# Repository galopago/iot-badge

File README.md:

# IOT-BADGE

## Electronic conference badge for programming conventions, hacking events, etc.

* Open Source (designed in [KiCad](https://www.kicad.org/)), schematic files, PCB and GERBER files open, free and available
* Comfortable wearable badge, no components on the back side.
* Max size 10 x 10 cm to take advantage of cost reductions of most PCB makers.
* Can be powered by a 3.2 v LiFePO4 AAA size battery
* Compatible with TinyGS firmware for [reception of LoRa satellites](https://galopago.github.io/english/lora-satelite-ground-station/). No modifications needed!

Read this in other languages: [Español](/iot-badge-433/assets/markdown/README.es.md)

## Block Diagram

## Capabilities

* ESP32 module compatible with multiple programming languages/platforms: [C/C++](https://docs.espressif.com/projects/esp-idf/en/latest/esp32/), [Arduino](https://github.com/espressif/arduino-esp32), Python (via [MicroPython](https://micropython.org/)), JavaScript (via [Espruino](https://www.espruino.com/ESP32) or [Mongoose OS](https://mongoose-os.com/)), [Rust ([via esp-rs](https://esp-rs.github.io/book/))
* 0.96" OLED display
* Infrared LED transmitter and receiver
* WiFi
* Radio transmitter and receiver module: FSK, GFSK, MSK, GMSK and LoRa!
* Onboard PCB antenna (433 Mhz and 915 Mhz versions)
* U.FL Connector for external antenna
* RGB LED
* 0.7 W speaker
* 6 buttons: 4 arranged in D-pad and 2 function buttons
* USB-C Connector

## 433 Mhz Version
Back                           | Side                                  | External Ant                          |
-------------------------------|---------------------------------------|---------------------------------------|
| | |

## Schematic Diagram 433 Version

## Pinout connections

### SSD1306 128x64 i2c OLED display

ESP32 GPIO PIN |Function
---------------|---------
4              | SDA
15             | SCL

### Ra-02 LoRa module

ESP32 GPIO PIN |Function
---------------|---------
19             | POCI
27             | PICO
5              | SCK
18             | /CS

### Speaker

ESP32 GPIO PIN |Function
---------------|---------
25             | Speaker

### Buttons ( please use internal pull-ups! )

ESP32 GPIO PIN |Function
---------------|---------
0              | Up
13             | Down
16             | Left
17             | Right
33             | B
32             | A

### RGB LED

ESP32 GPIO PIN |Function
---------------|---------
21             | Red
22             | Green
23             | Blue

### Ifrared transmitter LED

ESP32 GPIO PIN |Function
---------------|---------
2              | Infrared LED

### VS1838b INFRARED RECEIVER MODULE

ESP32 GPIO PIN |Function
---------------|---------
12             | VS1838b output

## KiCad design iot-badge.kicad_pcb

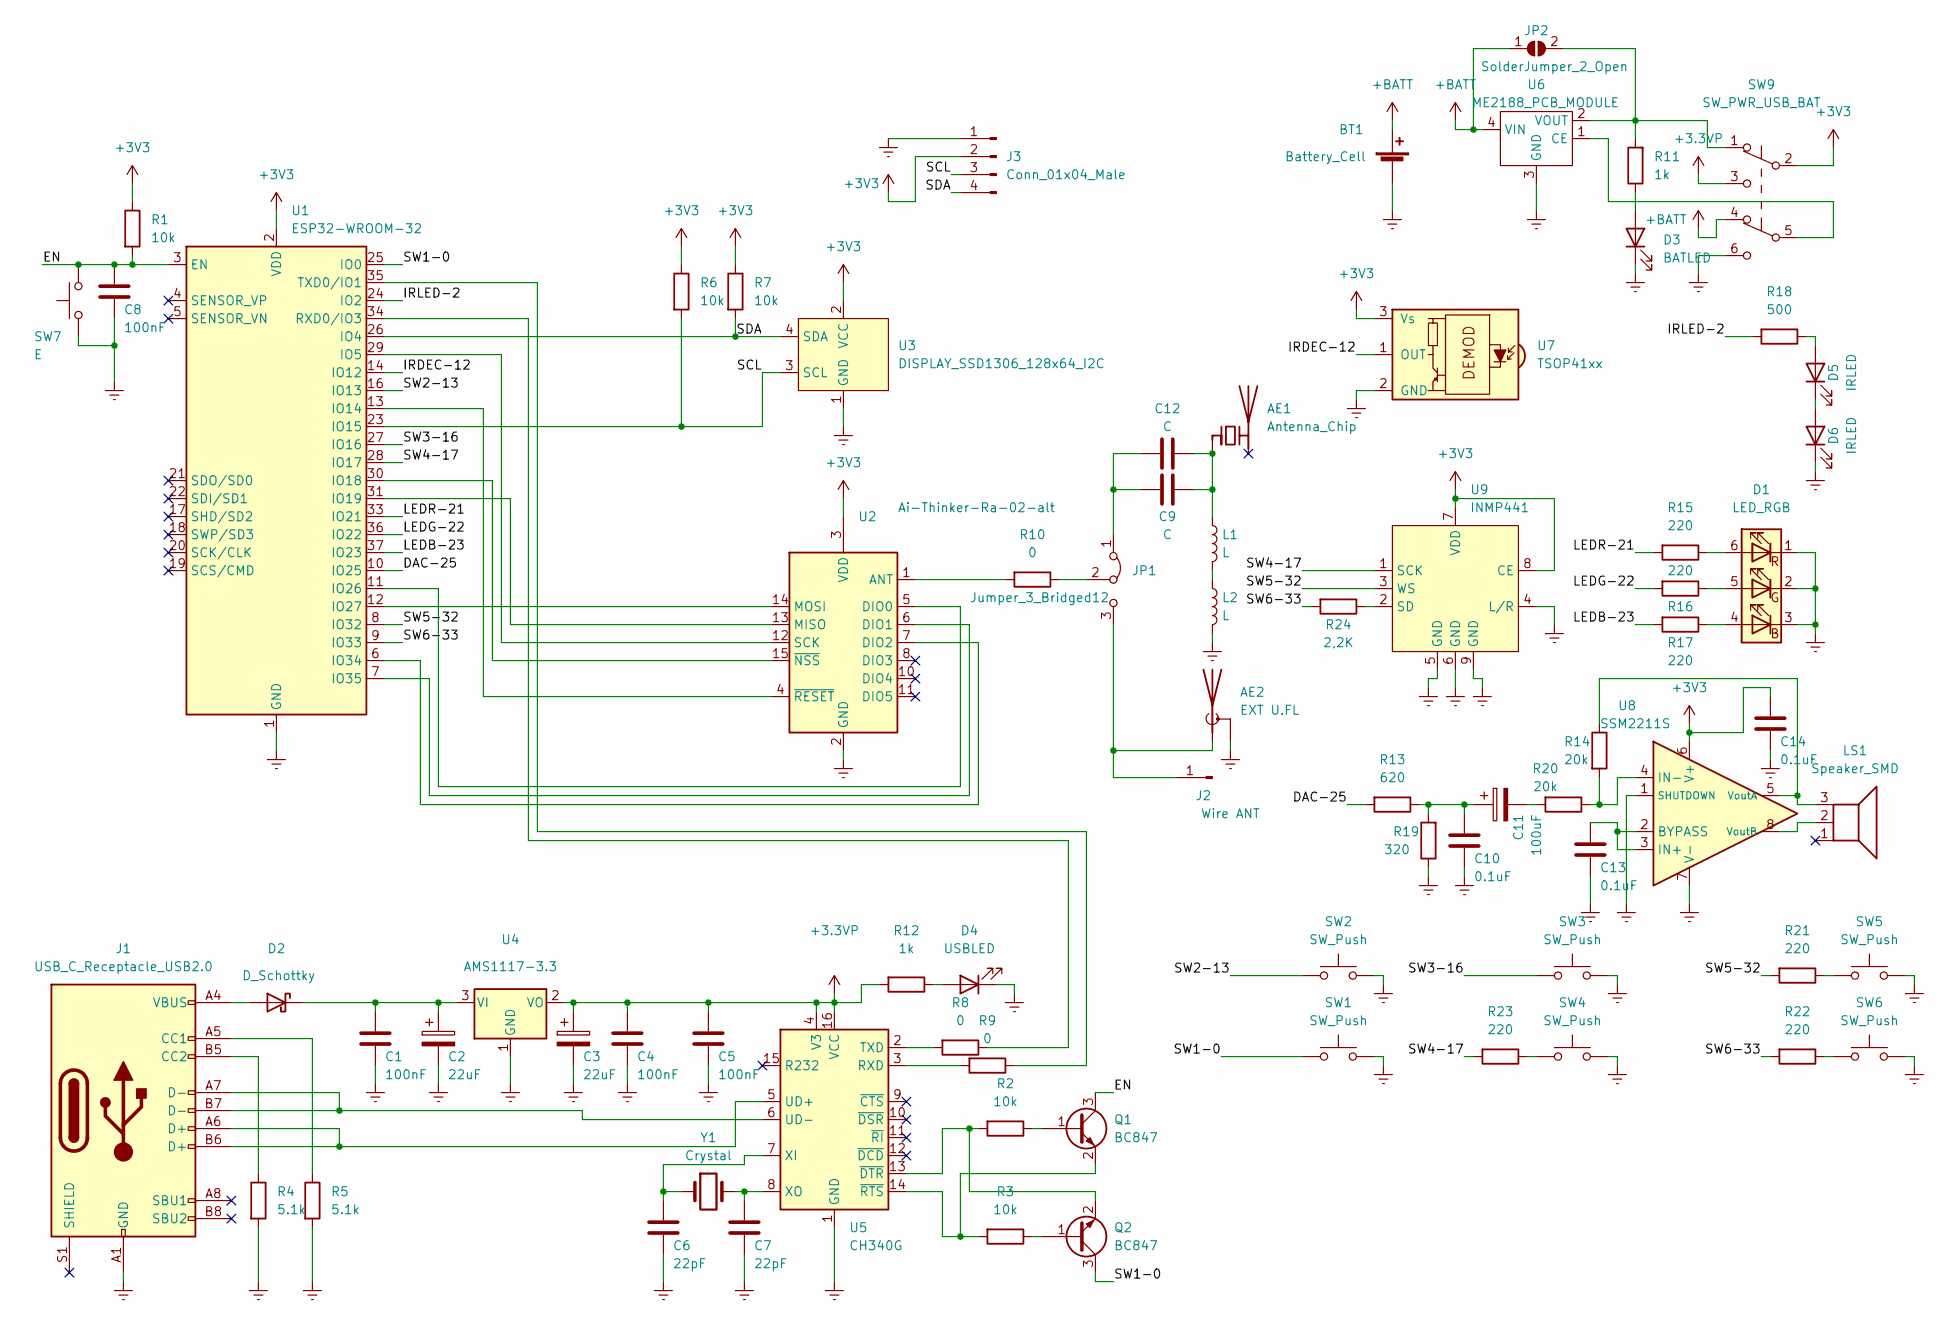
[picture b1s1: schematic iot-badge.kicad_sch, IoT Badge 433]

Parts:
AE1: Antenna_Chip; Crossair_ca-s01
AE2: EXT U.FL; U.FL_Hirose_U.FL-R-SMT-1_Vertical
BT1: Battery_Cell; BatteryHolder_Keystone_1022_2xAAA
C1, C4, C5, C8: 100nF; C_0805_2012Metric_Pad1.18x1.45mm_HandSolder
C2, C3: 22uF; CP_EIA-2012-15_AVX-P_Pad1.30x1.05mm_HandSolder
C6, C7: 22pF; C_0805_2012Metric_Pad1.18x1.45mm_HandSolder
C9, C12: C; C_0805_2012Metric_Pad1.18x1.45mm_HandSolder
C10, C13, C14: 0.1uF; C_0805_2012Metric_Pad1.18x1.45mm_HandSolder
C11: 100uF; CP_EIA-2012-15_AVX-P_Pad1.30x1.05mm_HandSolder
D1: LED_RGB; LED_RGB_5050-6
D2: D_Schottky; D_SOD-123
D3: BATLED; LED_0805_2012Metric_Pad1.15x1.40mm_HandSolder
D4: USBLED; LED_0805_2012Metric_Pad1.15x1.40mm_HandSolder
D5, D6: IRLED; LED_0805_2012Metric_Pad1.15x1.40mm_HandSolder
J1: USB_C_Receptacle_USB2.0; USB_C_Receptacle_HRO_TYPE-C-31-M-12
J2: Wire ANT; PinHeader_1x01_P1.00mm_Vertical
J3: Conn_01x04_Male; PinHeader_1x04_P2.54mm_Vertical
JP1: Jumper_3_Bridged12; SolderJumper-3_P1.3mm_Bridged12_RoundedPad1.0x1.5mm_NumberL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
JP2: SolderJumper_2_Open; SolderJumper-2_P1.3mm_Open_RoundedPad1.0x1.5mm
L1, L2: L; L_0805_2012Metric_Pad1.05x1.20mm_HandSolder
LS1: Speaker_SMD; Speaker_SMD-5020
Q1, Q2: BC847; SOT-23
R1, R2, R3, R6, R7: 10k; R_0805_2012Metric_Pad1.20x1.40mm_HandSolder
R4, R5: 5.1k; R_0805_2012Metric_Pad1.20x1.40mm_HandSolder
R8, R9, R10: 0; R_0805_2012Metric_Pad1.20x1.40mm_HandSolder
R11, R12: 1k; R_0805_2012Metric_Pad1.20x1.40mm_HandSolder
R13: 620; R_0805_2012Metric_Pad1.20x1.40mm_HandSolder
R14, R20: 20k; R_0805_2012Metric_Pad1.20x1.40mm_HandSolder
R15, R16, R17, R21, R22, R23: 220; R_0805_2012Metric_Pad1.20x1.40mm_HandSolder
R18: 500; R_0805_2012Metric_Pad1.20x1.40mm_HandSolder
R19: 320; R_0805_2012Metric_Pad1.20x1.40mm_HandSolder
R24: 2,2K; R_0805_2012Metric_Pad1.20x1.40mm_HandSolder
SW1, SW2, SW3, SW4, SW5, SW6: SW_Push; SW_Push_1P1T_NO_6x6mm_H9.5mm
SW7: E; SW_Push_SPST_NO_Alps_SKRK
SW9: SW_PWR_USB_BAT; SW_Slide_2P2T_9mmx7.6mm
U1: ESP32-WROOM-32
U2: Ai-Thinker-Ra-02-alt; Ai-Thinker-Ra-02-LoRa-alt
U3: DISPLAY_SSD1306_128x64_I2C; DISPLAY_SSD1306_128x64_I2C_0.96inch
U4: AMS1117-3.3; SOT-223-3_TabPin2
U5: CH340G; SOIC-16_3.9x9.9mm_P1.27mm
U6: ME2188_PCB_MODULE
U7: TSOP41xx; Vishay_MOLD-3Pin
U8: SSM2211S; SOIC-8_3.9x4.9mm_P1.27mm
U9: INMP441
Y1: Crystal; Crystal_SMD_HC49-SD_HandSoldering_Compact

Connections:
+3.3VP: C3.1, C4.1, C5.1, R12.2, SW9.3 (C), U4.2 (VO), U5.4 (V3), U5.16 (VCC)
+3V3: C14.1, J3.2, R1.1, R6.1, R7.1, SW9.2 (B), U1.2 (VDD), U2.3 (VDD), U3.2 (VCC), U7.3 (Vs), U8.6 (V+), U9.7 (VDD), U9.8 (CE)
+BATT: BT1.1 (+), JP2.1 (A), SW9.4 (A), U6.4 (VIN)
/DAC-25: R13.2, U1.10 (IO25)
/EN: C8.1, Q1.3 (C), R1.2, SW7.2, U1.3 (EN)
/IRDEC-12: U1.14 (IO12), U7.1 (OUT)
/IRLED-2: R18.2, U1.24 (IO2)
/LEDB-23: R17.2, U1.37 (IO23)
/LEDG-22: R16.2, U1.36 (IO22)
/LEDR-21: R15.2, U1.33 (IO21)
/SCL: J3.3, R6.2, U1.23 (IO15), U3.3 (SCL)
/SDA: J3.4, R7.2, U1.26 (IO4), U3.4 (SDA)
/SW1-0: Q2.3 (C), SW1.1, U1.25 (IO0)
/SW2-13: SW2.1, U1.16 (IO13)
/SW3-16: SW3.1, U1.27 (IO16)
/SW4-17: R23.2, U1.28 (IO17), U9.1 (SCK)
/SW5-32: R21.2, U1.8 (IO32), U9.3 (WS)
/SW6-33: R22.2, R24.2, U1.9 (IO33)
Earth: AE2.2 (Shield), BT1.2 (-), C1.2, C2.2, C3.2, C4.2, C5.2, C6.2, C7.2, C8.2, C10.2, C13.2, C14.2, D1.1 (RK), D1.2 (GK), D1.3 (BK), D3.1 (K), D4.1 (K), D6.1 (K), J1.A1 (GND), J1.A12 (GND), J1.B1 (GND), J1.B12 (GND), J3.1, L2.2, R4.2, R5.2, R19.1, SW1.2, SW2.2, SW3.2, SW4.2, SW5.2, SW6.2, SW7.1, SW9.6 (C), U1.1 (GND), U1.15 (GND), U1.38 (GND), U1.39 (GND), U2.2 (GND), U2.9 (GND), U2.16 (GND), U3.1 (GND), U4.1 (GND), U5.1 (GND), U6.3 (GND), U7.2 (GND), U8.1 (SHUTDOWN), U8.7 (V-), U9.4 (L/R), U9.5 (GND), U9.6 (GND), U9.9 (GND)
unnamed: AE1.1 (FEED), C9.1, C12.1, L1.1
unnamed: AE2.1 (A), J2.1, JP1.3 (B)
unnamed: C1.1, C2.1, D2.1 (K), U4.3 (VI)
unnamed: C6.1, U5.7 (XI), Y1.1
unnamed: C7.1, U5.8 (XO), Y1.2
unnamed: C10.1, C11.1, R13.1, R19.2
unnamed: C11.2, R20.2
unnamed: C9.2, C12.2, JP1.1 (A)
unnamed: C13.1, U8.2 (BYPASS), U8.3 (IN+)
unnamed: D1.4 (BA), R17.1
unnamed: D1.5 (GA), R16.1
unnamed: D1.6 (RA), R15.1
unnamed: D2.2 (A), J1.A4 (VBUS), J1.A9 (VBUS), J1.B4 (VBUS), J1.B9 (VBUS)
unnamed: D3.2 (A), R11.1
unnamed: D4.2 (A), R12.1
unnamed: D5.1 (K), D6.2 (A)
unnamed: D5.2 (A), R18.1
unnamed: J1.A5 (CC1), R5.1
unnamed: J1.A6 (D+), J1.B6 (D+), U5.5 (UD+)
unnamed: J1.A7 (D-), J1.B7 (D-), U5.6 (UD-)
unnamed: J1.B5 (CC2), R4.1
unnamed: JP1.2 (C), R10.1
unnamed: JP2.2 (B), R11.2, SW9.1 (A), U6.2 (VOUT)
unnamed: L1.2, L2.1
unnamed: LS1.2, U8.8 (VoutB)
unnamed: LS1.3, R14.1, U8.5 (VoutA)
unnamed: Q1.1 (B), R2.1
unnamed: Q1.2 (E), R3.2, U5.14 (~RTS)
unnamed: Q2.1 (B), R3.1
unnamed: Q2.2 (E), R2.2, U5.13 (~DTR)
unnamed: R8.1, U1.34 (RXD0/IO3)
unnamed: R8.2, U5.2 (TXD)
unnamed: R9.1, U1.35 (TXD0/IO1)
unnamed: R9.2, U5.3 (RXD)
unnamed: R10.2, U2.1 (ANT)
unnamed: R14.2, R20.1, U8.4 (IN-)
unnamed: R21.1, SW5.1
unnamed: R22.1, SW6.1
unnamed: R23.1, SW4.1
unnamed: R24.1, U9.2 (SD)
unnamed: SW9.5 (B), U6.1 (CE)
unnamed: U1.6 (IO34), U2.7 (DIO2)
unnamed: U1.7 (IO35), U2.6 (DIO1)
unnamed: U1.11 (IO26), U2.5 (DIO0)
unnamed: U1.12 (IO27), U2.14 (MOSI)
unnamed: U1.13 (IO14), U2.4 (~RESET)
unnamed: U1.29 (IO5), U2.12 (SCK)
unnamed: U1.30 (IO18), U2.15 (~NSS)
unnamed: U1.31 (IO19), U2.13 (MISO)

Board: 2 copper layers, 77 parts (1 on the bottom side), 68 nets, no tracks yet.

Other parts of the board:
SYMB1: OSHW-Symbol_6.7x6mm_Copper
SYMB2: OSHW-Symbol_6.7x6mm_SilkScreen

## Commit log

2023-01-29 added first proof of concept
2023-01-29 added first blockdiag
2023-02-26 added mic to blockdiag
2023-02-27 started readme
2023-02-27 started readme+
2023-03-01 started micrel pcb helix ant 433
2023-03-07 pcb antenna finished
2023-03-09 i2c display footprint started
2023-03-14 improved holding holes
2023-03-14 changed battery for AAA
2023-03-15 added some USB components
2023-03-22 ant needs some care NETS
2023-03-25 ant needs routing rules
2023-03-26 pcb ant fixed
2023-03-29 connected lora and screen
2023-03-31 added res buttons and almost routable
2023-04-19 added crystal and led rgb
2023-04-21 diode added to power
2023-04-26 added external ant
2023-04-29 power switch added
2023-05-01 added ground to pushbuttons
2023-05-02 started batt footprint
2023-05-03 all elements placed and wired
2023-05-04 silk improvements
2023-05-05 all wired, unable to route
2023-05-06 all wired, routed
2023-05-06 all wired, routed,fixes
2023-05-08 finished pcb
2023-05-08 gerber single
2023-06-08 started pinout
2023-06-08 more pinouts
2023-06-08 pinout table finished
2023-06-08 typo
2023-06-12 started readme EN
2023-06-12 adding pics to readme EN
2023-06-12 adding pics to readme EN schem
2023-06-12 EN radme mvp finished
2023-06-12 EN more pics
2023-06-12 EN more pics+
2023-06-12 EN more pics++
2023-06-12 EN more pics rotated
2023-06-12 started readme ES
2023-06-12 finished readme ES text
2023-07-03 added pdf dc boost prospect
2023-07-03 started 915 mhz pcb antenna
2023-07-03 finished uhf pcb antenna
2023-07-03 created iot badge VHF
2023-07-03 created iot 433 and 915 versions (renamed)
2023-07-03 915 version finished
2023-07-04 433 gerbers ok
2023-07-04 915 gerbers ok
2023-07-04 adapting readme for 433 and 915 versions
2023-07-04 updating readme
2023-07-04 updating readme+
2023-07-04 updating readme++
2023-07-04 updating readme+++
2023-07-04 updating readme++++
2023-07-04 updating readme ES
2023-07-04 updating readme ES+
2023-07-04 updating readme ES++
2023-07-04 updating readme ES+++
2023-07-04 updating readme ES++++
2023-07-14 started smd 5020 buzzer footprint
2023-07-20 changed ir leds polarity, PSU silk and bypass jumper
2023-07-20 added external i2c pins
2023-07-20 shifted ant match elements to the left
2023-07-21 added tuning cap an inductor to ant circuit
2023-07-22 enlarged AAA bat footprint pads
2023-08-13 added BTL amp to schematic
2023-08-13 audio amp elements routed
2023-08-15 added and routed audio components in 915mhz
2023-08-21 added i2s mems mic schematic and footprint
2023-08-22 moved xtal capacitors to make some room
2023-08-22 added resistors to sw to protect against shorts
2023-08-26 moved capacitors to make room
2023-08-28 added resistor to switch
2023-08-28 added i2s mic symbol
2023-08-28 placed i2c mic in pcb
2023-08-29 finished placing i2s mic
2023-08-30 added some silk lines on back 433
2023-08-31 added silks to 915 board
2023-08-31 433 gerber
2023-09-02 915 mhz single gerber
2023-11-07 started to add new parts
2023-11-08 aligned cross buttons
2023-12-06 fixed crystal footprint and placed all components ok
